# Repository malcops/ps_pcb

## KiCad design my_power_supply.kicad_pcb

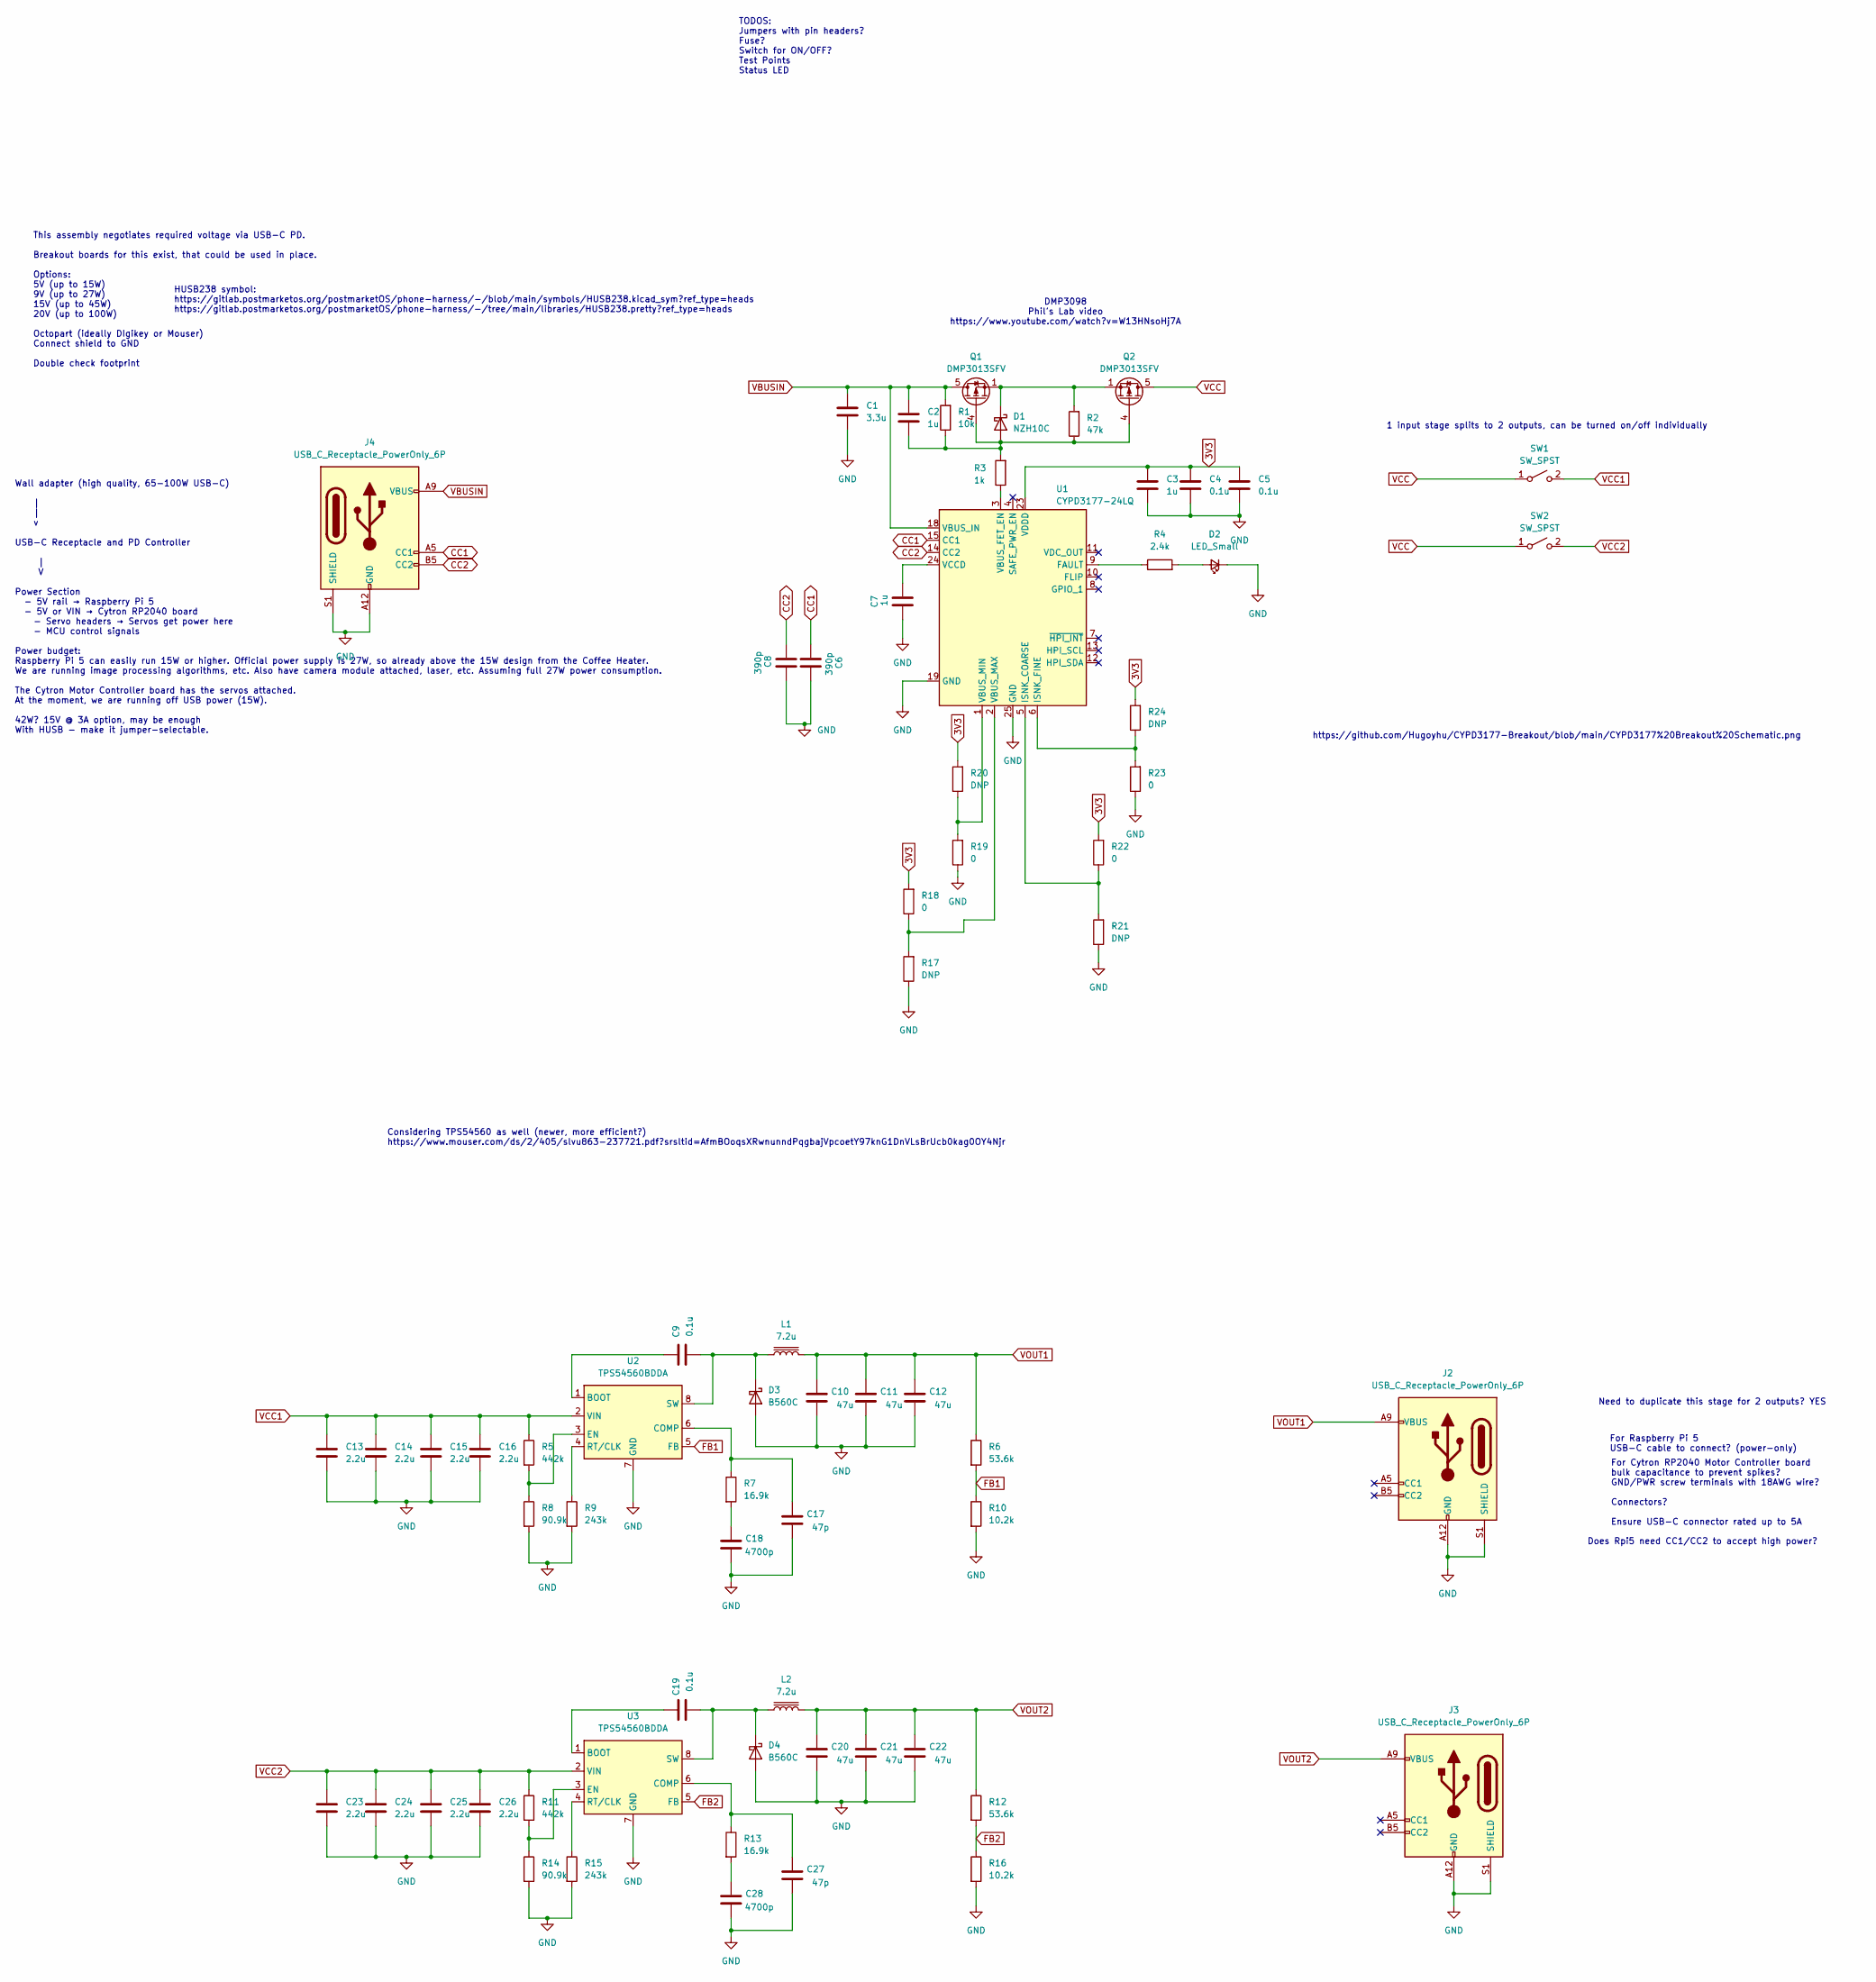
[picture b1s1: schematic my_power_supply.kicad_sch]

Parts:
C1: 3.3u; C_1206_3216Metric
C2, C3, C7: 1u; C_1206_3216Metric
C4, C5, C9, C19: 0.1u; C_1206_3216Metric
C6, C8: 390p; C_1206_3216Metric
C10, C11, C12, C20, C21, C22: 47u; C_1206_3216Metric
C13, C14, C15, C16, C23, C24, C25, C26: 2.2u; C_1206_3216Metric
C17, C27: 47p; C_1206_3216Metric
C18, C28: 4700p; C_1206_3216Metric
D1: NZH10C; D_SOD-323F
D2: LED_Small; LED_1206_3216Metric_Pad1.42x1.75mm_HandSolder
D3, D4: B560C; SMC_DIO
J2, J3, J4: USB_C_Receptacle_PowerOnly_6P; USB_C_Plug_Molex_105444
L1, L2: 7.2u; L_Wurth_WE-PDF-1045
Q1, Q2: DMP3013SFV; Diodes_PowerDI3333-8
R1: 10k; R_1206_3216Metric
R2: 47k; R_1206_3216Metric
R3: 1k; R_1206_3216Metric
R4: 2.4k; R_1206_3216Metric
R5, R11: 442k; R_1206_3216Metric
R6, R12: 53.6k; R_1206_3216Metric
R7, R13: 16.9k; R_1206_3216Metric
R8, R14: 90.9k; R_1206_3216Metric
R9, R15: 243k; R_1206_3216Metric
R10, R16: 10.2k; R_1206_3216Metric
R17, R20, R21, R24: DNP; R_0805_2012Metric
R18, R19, R22, R23: 0; R_0805_2012Metric
SW1, SW2: SW_SPST; SW_DIP_SPSTx01_Slide_9.78x4.72mm_W8.61mm_P2.54mm
U1: CYPD3177-24LQ; QFN-24-1EP_4x4mm_P0.5mm_EP2.75x2.75mm
U2, U3: TPS54560BDDA; Texas_R-PDSO-G8_EP2.95x4.9mm_Mask2.4x3.1mm_ThermalVias

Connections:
3V3: C3.1, C4.1, C5.1, R18.2, R20.2, R22.2, R24.2, U1.23 (VDDD)
CC1: C6.1, J4.A5 (CC1), U1.15 (CC1)
CC2: C8.1, J4.B5 (CC2), U1.14 (CC2)
FB1: R6.2, R10.1, U2.5 (FB)
FB2: R12.2, R16.1, U3.5 (FB)
GND: C1.2, C3.2, C4.2, C5.2, C6.2, C7.1, C8.2, C10.1, C11.1, C12.1, C13.2, C14.2, C15.2, C16.2, C17.1, C18.1, C20.1, C21.1, C22.1, C23.2, C24.2, C25.2, C26.2, C27.1, C28.1, D2.1 (K), D3.2 (A), D4.2 (A), J2.A12 (GND), J2.B12 (GND), J2.S1 (SHIELD), J3.A12 (GND), J3.B12 (GND), J3.S1 (SHIELD), J4.A12 (GND), J4.B12 (GND), J4.S1 (SHIELD), R8.2, R9.2, R10.2, R14.2, R15.2, R16.2, R17.1, R19.1, R21.1, R23.1, U1.19 (GND), U1.22 (GND), U1.25 (GND), U2.7 (GND), U2.9 (GND), U3.7 (GND), U3.9 (GND)
unnamed: C18.2, R7.2
unnamed: C28.2, R13.2
unnamed: C2.2, D1.2 (A), Q1.4 (G), Q2.4 (G), R1.1, R2.1, R3.2
unnamed: D1.1 (K), Q1.1 (S), Q1.2 (S), Q1.3 (S), Q2.1 (S), Q2.2 (S), Q2.3 (S), R2.2
unnamed: D2.2 (A), R4.2
unnamed: C9.1, D3.1 (K), L1.1, U2.8 (SW)
unnamed: C19.1, D4.1 (K), L2.1, U3.8 (SW)
unnamed: R4.1, U1.9 (FAULT)
unnamed: R21.2, R22.1, U1.5 (ISNK_COARSE)
unnamed: R23.2, R24.1, U1.6 (ISNK_FINE)
unnamed: R3.1, U1.3 (VBUS_FET_EN)
unnamed: R17.2, R18.1, U1.2 (VBUS_MAX)
unnamed: R19.2, R20.1, U1.1 (VBUS_MIN)
unnamed: C7.2, U1.24 (VCCD)
unnamed: C9.2, U2.1 (BOOT)
unnamed: C17.2, R7.1, U2.6 (COMP)
unnamed: R5.2, R8.1, U2.3 (EN)
unnamed: R9.1, U2.4 (RT/CLK)
unnamed: C19.2, U3.1 (BOOT)
unnamed: C27.2, R13.1, U3.6 (COMP)
unnamed: R11.2, R14.1, U3.3 (EN)
unnamed: R15.1, U3.4 (RT/CLK)
VBUSIN: C1.1, C2.1, J4.A9 (VBUS), J4.B9 (VBUS), Q1.5 (D), R1.2, U1.18 (VBUS_IN)
VCC: Q2.5 (D), SW1.1 (A), SW2.1 (A)
VCC1: C13.1, C14.1, C15.1, C16.1, R5.1, SW1.2 (B), U2.2 (VIN)
VCC2: C23.1, C24.1, C25.1, C26.1, R11.1, SW2.2 (B), U3.2 (VIN)
VOUT1: C10.2, C11.2, C12.2, J2.A9 (VBUS), J2.B9 (VBUS), L1.2, R6.1
VOUT2: C20.2, C21.2, C22.2, J3.A9 (VBUS), J3.B9 (VBUS), L2.2, R12.1

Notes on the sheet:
Does Rpi5 need CC1/CC2 to accept high power?
https://github.com/Hugoyhu/CYPD3177-Breakout/blob/main/CYPD3177%20Breakout%20Schematic.png
TODOS: Jumpers with pin headers? Fuse? Switch for ON/OFF? Test Points Status LED
Considering TPS54560 as well (newer, more efficient?) https://www.mouser.com/ds/2/405/slvu863-237721.pdf?srsltid=AfmBOoqsXRwnunndPqgbajVpcoetY97knG1DnVLsBrUcb0kag0OY4Njr
This assembly negotiates required voltage via USB-C PD. Breakout boards for this exist, that could be used in place. Options: 5V (up to 15W) 9V (up to 27W) 15V (up to 45W) 20V (up to 100W) Octopart (ideally DIgikey or Mouser) Connect shield to GND Double check footprint
Need to duplicate this stage for 2 outputs? YES
HUSB238 symbol: https://gitlab.postmarketos.org/postmarketOS/phone-harness/-/blob/main/symbols/HUSB238.kicad_sym?ref_type=heads https://gitlab.postmarketos.org/postmarketOS/phone-harness/-/tree/main/libraries/HUSB238.pretty?ref_type=heads
Wall adapter (high quality, 65-100W USB-C) | | v USB-C Receptacle and PD Controller | V Power Section - 5V rail → Raspberry Pi 5 - 5V or VIN → Cytron RP2040 board - Servo headers → Servos get power here - MCU control signals Power budget: Raspberry Pi 5 can easily run 15W or higher. Official power 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
For Raspberry Pi 5 USB-C cable to connect? (power-only)
1 input stage splits to 2 outputs, can be turned on/off individually
DMP3098 Phil's Lab video https://www.youtube.com/watch?v=W13HNsoHj7A
For Cytron RP2040 Motor Controller board bulk capacitance to prevent spikes? GND/PWR screw terminals with 18AWG wire? Connectors? Ensure USB-C connector rated up to 5A

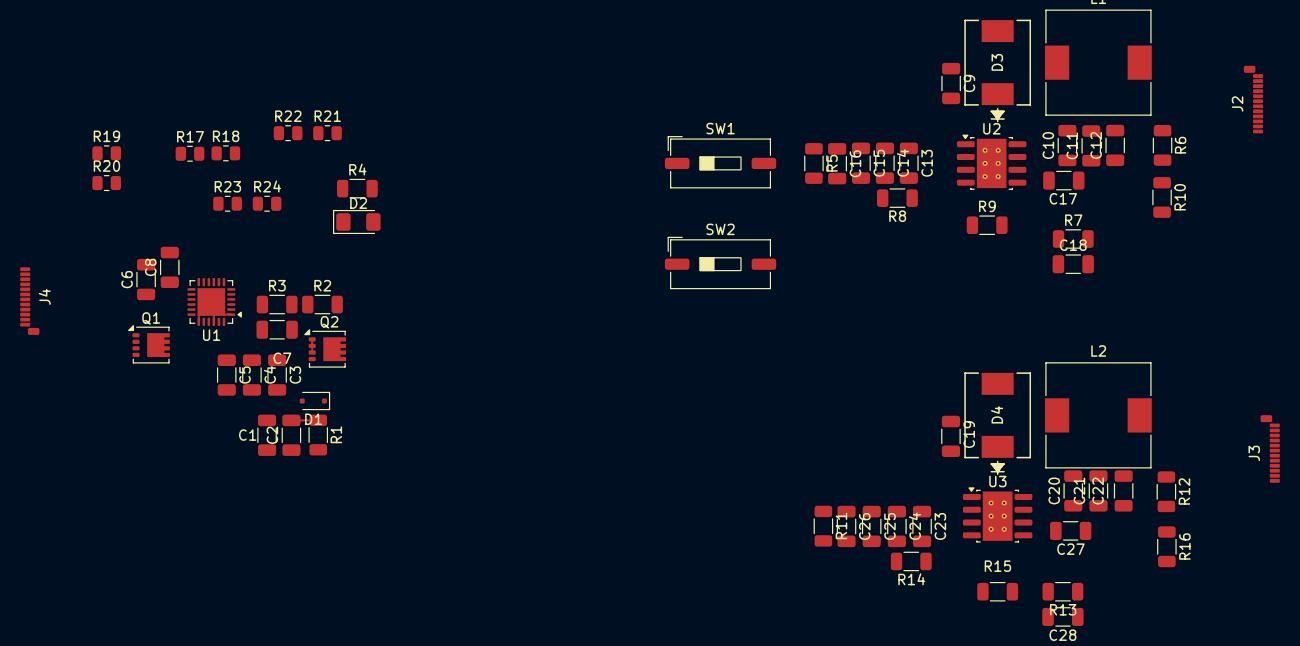
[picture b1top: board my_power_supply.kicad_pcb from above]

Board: 2 copper layers, 68 parts (0 on the bottom side), 34 nets.
